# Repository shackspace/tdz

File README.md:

Teleduschzelle
==============

Teleduschzelle (phone shower cabin) is a project exco made happen @shackspace Stuttgart
 
http://shackspace.de/wiki/doku.php?id=project:teleduschzelle

Code will eventually appear here as well.

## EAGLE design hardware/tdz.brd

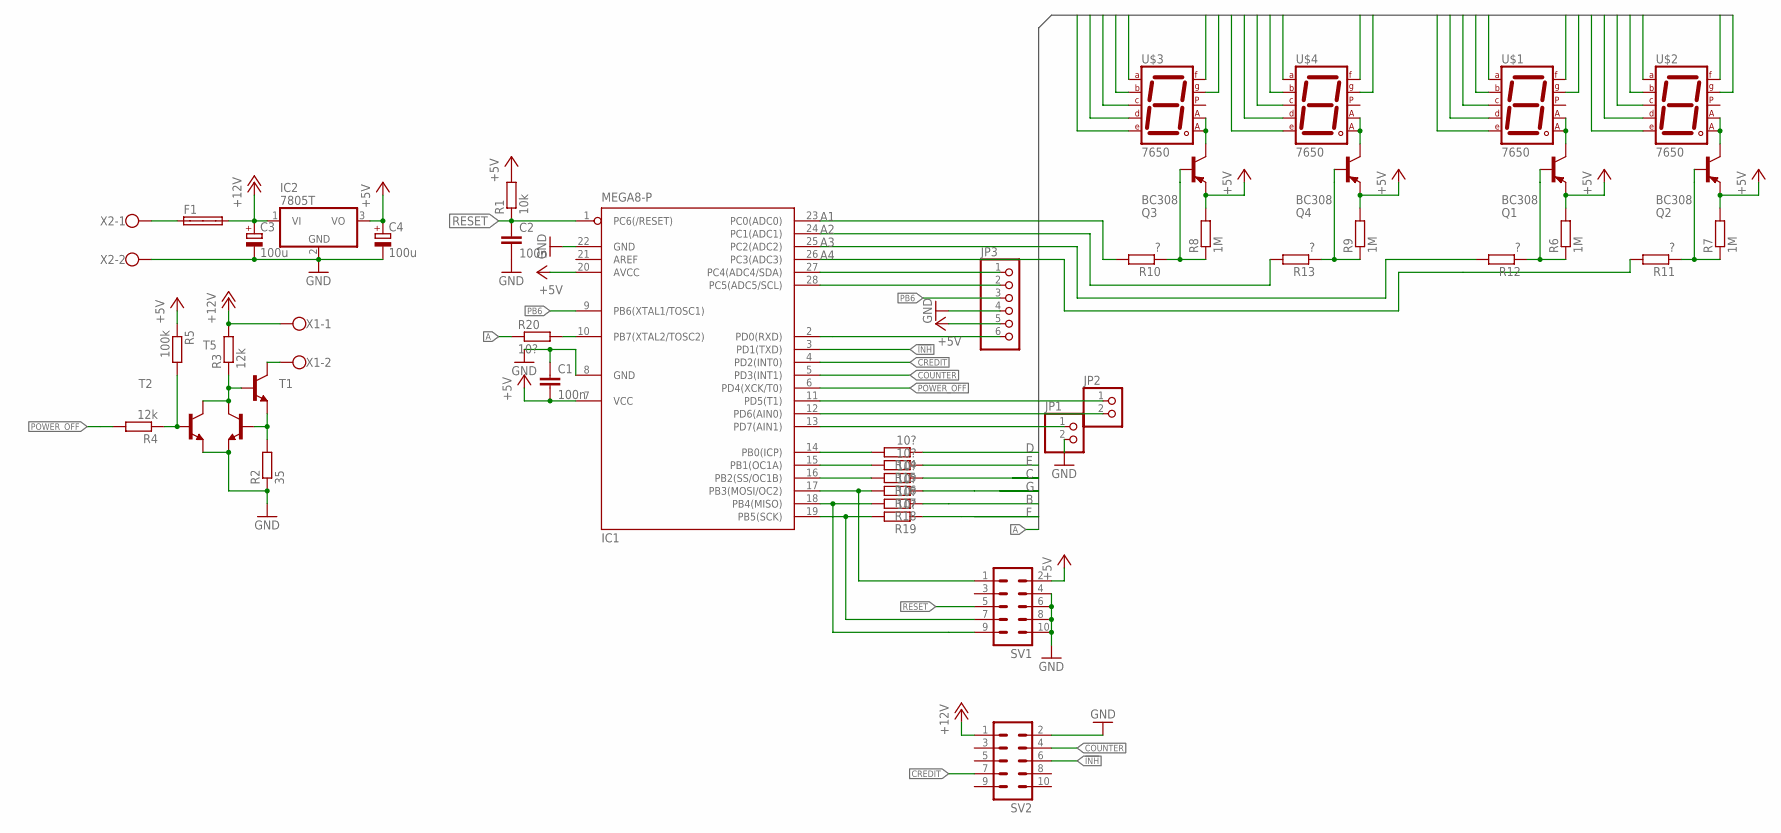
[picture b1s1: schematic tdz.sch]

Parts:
C1, C2: 100n; C0603
C3, C4: 100u; E22-9
F1: SHK20Q
IC1: MEGA8-P; DIL28-3
IC2: 7805T; TO220H
JP1, JP2: PINHD-1X02_2.54-S; 1X02-S
JP3: PINHD-1X6; 1X06
Q1, Q2, Q3, Q4: BC308; TO92-EBC
R1: 10k; R0603
R2: 35; R0603
R3, R4: 12k; R0603
R5: 100k; R0603
R6, R7, R8, R9: 1M; R0603
R10, R11, R12, R13: ?; 0207/7
R14, R15, R16, R17, R18, R19, R20: 10?; R0603
SV1, SV2: ML10L
T1, T2, T5: BC548-NPN-TO92-CBE; TO92-CBE
U$1, U$2, U$3, U$4: 7650
X1, X2: W237-102

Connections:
!INH!: IC1.3 (PD1(TXD)), SV2.6
+5V: C1.2, C4.+, IC1.7 (VCC), IC1.20 (AVCC), IC2.3 (VO), JP3.5, Q1.E, Q2.E, Q3.E, Q4.E, R1.2, R5.1, R6.2, R7.2, R8.2, R9.2, SV1.2
+12V: C3.+, F1.2A, IC2.1 (VI), R3.2, SV2.1, X1.1
A: R20.1, U$1.P$1 (A), U$2.P$1 (A), U$3.P$1 (A), U$4.P$1 (A)
A1: IC1.23 (PC0(ADC0)), R10.2
A2: IC1.24 (PC1(ADC1)), R13.2
A3: IC1.25 (PC2(ADC2)), R12.2
A4: IC1.26 (PC3(ADC3)), R11.2
B: R18.1, U$1.P$13 (B), U$2.P$13 (B), U$3.P$13 (B), U$4.P$13 (B)
C: R16.1, U$1.P$10 (C), U$2.P$10 (C), U$3.P$10 (C), U$4.P$10 (C)
COUNTER: IC1.5 (PD3(INT1)), SV2.4
CREDIT: IC1.4 (PD2(INT0)), SV2.7
D: R14.1, U$1.P$8 (D), U$2.P$8 (D), U$3.P$8 (D), U$4.P$8 (D)
E: R15.1, U$1.P$7 (E), U$2.P$7 (E), U$3.P$7 (E), U$4.P$7 (E)
F: R19.1, U$1.P$2 (F), U$2.P$2 (F), U$3.P$2 (F), U$4.P$2 (F)
G: R17.1, U$1.P$11 (G), U$2.P$11 (G), U$3.P$11 (G), U$4.P$11 (G)
GND: C1.1, C2.2, C3.-, C4.-, IC1.8 (GND), IC1.22 (GND), IC2.2 (GND), JP1.2, JP3.4, R2.1, SV1.4, SV1.6, SV1.8, SV1.10, SV2.2, T1.E, T2.E, X2.2
unnamed: Q1.C, U$1.P$3 (CA1), U$1.P$14 (CA2)
unnamed: Q2.C, U$2.P$3 (CA1), U$2.P$14 (CA2)
unnamed: Q3.C, U$3.P$3 (CA1), U$3.P$14 (CA2)
unnamed: Q4.C, U$4.P$3 (CA1), U$4.P$14 (CA2)
unnamed: Q4.B, R9.1, R13.1
unnamed: Q3.B, R8.1, R10.1
unnamed: Q2.B, R7.1, R11.1
unnamed: Q1.B, R6.1, R12.1
unnamed: T5.C, X1.2
unnamed: IC1.13 (PD7(AIN1)), JP1.1
unnamed: IC1.12 (PD6(AIN0)), JP2.2
unnamed: R2.2, T1.B, T5.E
unnamed: IC1.11 (PD5(T1)), JP2.1
unnamed: R3.1, T1.C, T2.C, T5.B
unnamed: R4.1, R5.2, T2.B
unnamed: IC1.10 (PB7(XTAL2/TOSC2)), R20.2
unnamed: IC1.14 (PB0(ICP)), R14.2
unnamed: IC1.15 (PB1(OC1A)), R15.2
unnamed: IC1.16 (PB2(SS/OC1B)), R16.2
unnamed: IC1.18 (PB4(MISO)), R18.2, SV1.9
unnamed: IC1.19 (PB5(SCK)), R19.2, SV1.7
unnamed: IC1.17 (PB3(MOSI/OC2)), R17.2, SV1.1
unnamed: IC1.27 (PC4(ADC4/SDA)), JP3.1
unnamed: IC1.28 (PC5(ADC5/SCL)), JP3.2
unnamed: IC1.2 (PD0(RXD)), JP3.6
unnamed: F1.1A, X2.1
PB6: IC1.9 (PB6(XTAL1/TOSC1)), JP3.3
POWER_OFF: IC1.6 (PD4(XCK/T0)), R4.2
RESET: C2.1, IC1.1 (PC6(/RESET)), R1.1, SV1.5

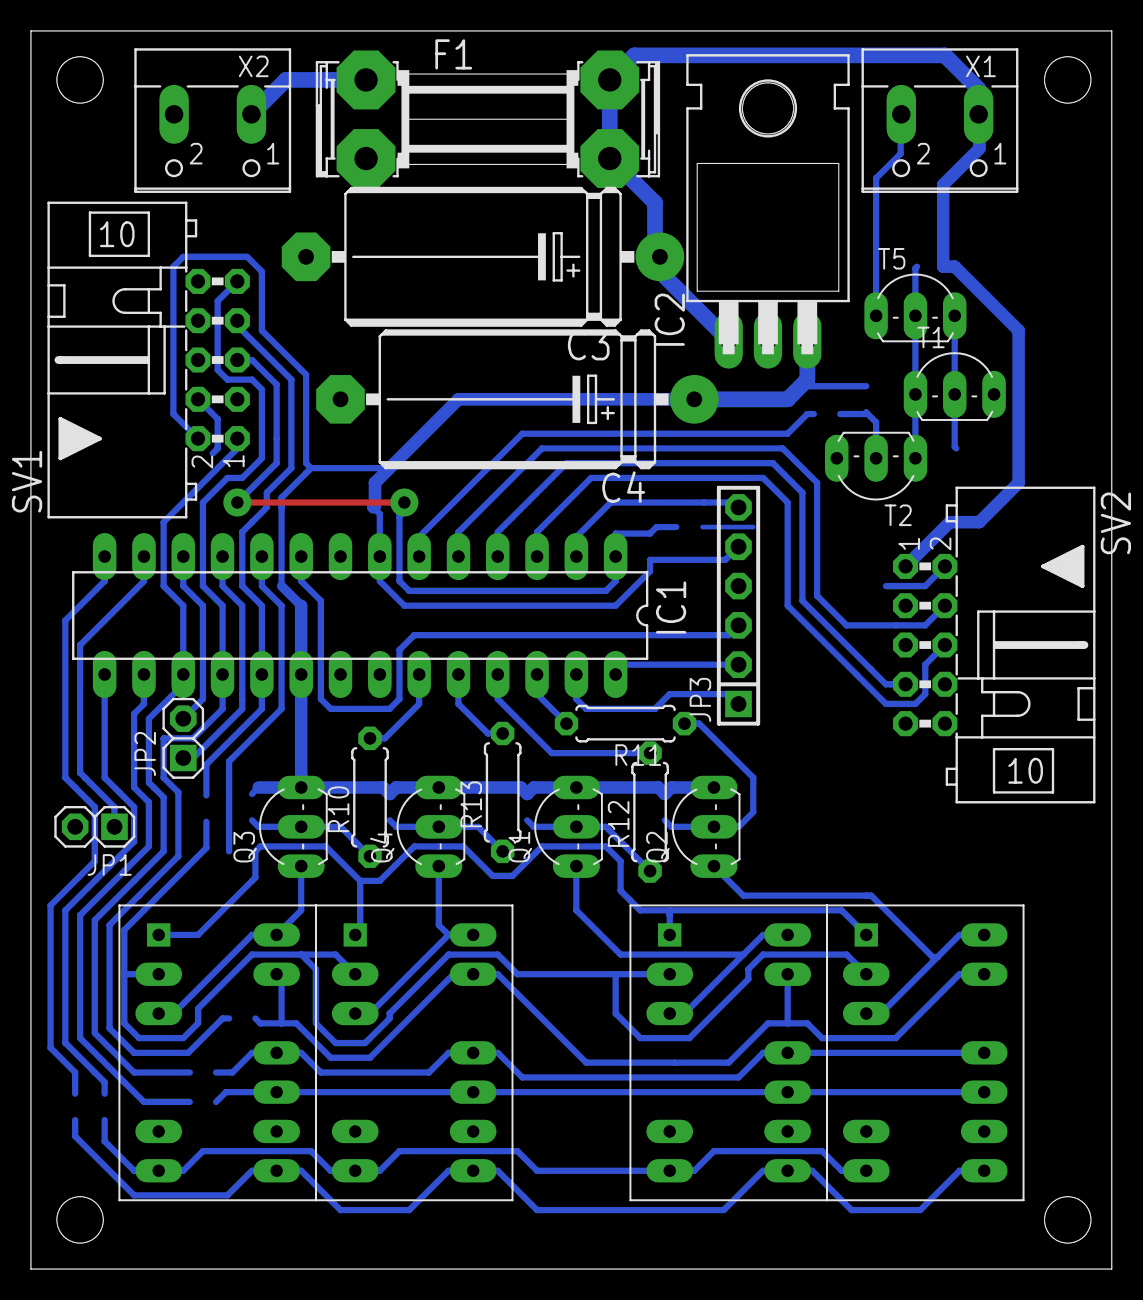
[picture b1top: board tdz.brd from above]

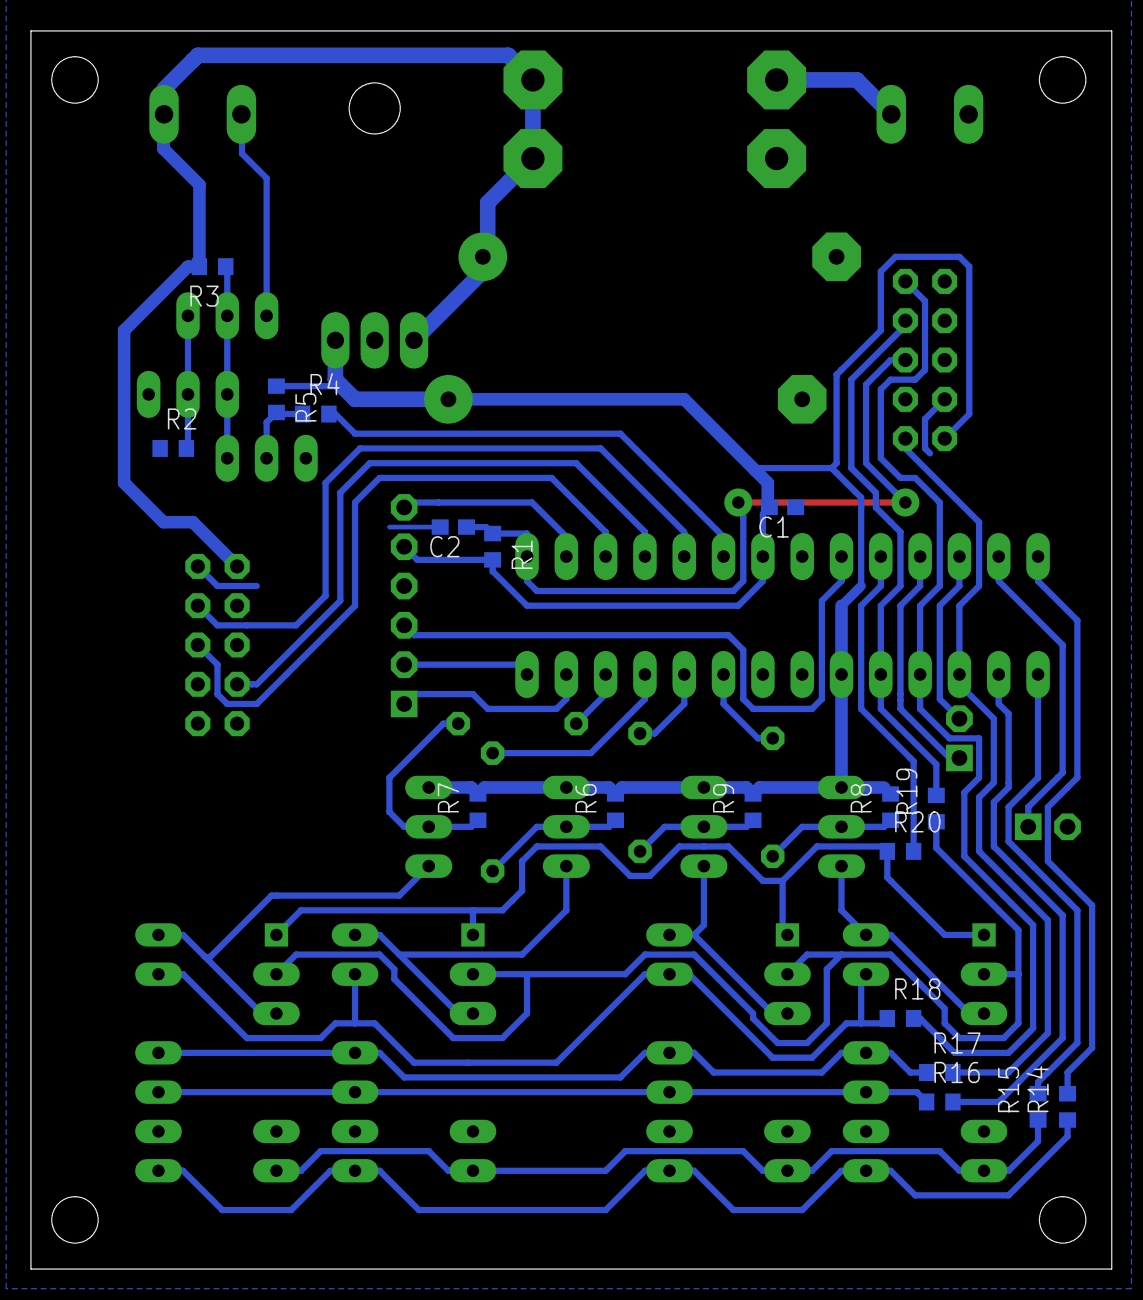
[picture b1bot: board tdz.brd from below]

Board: 2 copper layers, 69.8 x 80.0 mm, 45 parts (18 on the bottom side), 46 nets.

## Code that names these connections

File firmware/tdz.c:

/*
 * tdz.c
 *
 * Created: 14.06.2013 00:23:12
 *  Author: alex
 */


#include <avr/io.h>
#include <avr/interrupt.h>
#include <avr/pgmspace.h>
#include <avr/cpufunc.h>
#include <util/delay.h>
#include <string.h>

#define D	1<<PB0
#define E	1<<PB1
#define C	1<<PB2
#define G	1<<PB3
#define B	1<<PB4
#define F	1<<PB5
#define A	1<<PB7

#define S_0	(A|B|C|D|E|F)
#define S_1	(B|C)
#define S_2	(A|B|D|E|G)
#define S_3	(A|B|C|D|G)
#define S_4	(B|C|F|G)
#define S_5	(A|C|D|F|G)
#define S_6	(A|C|D|E|F|G)
#define S_7	(A|B|C)
#define S_8	(A|B|C|D|E|F|G)
#define S_9	(A|B|C|D|F|G)
#define S_E	(A|D|E|F|G)

const uint8_t symbols[] PROGMEM = {S_0,S_1,S_2,S_3,S_4,S_5,S_6,S_7,S_8,S_9};

#define T1_PRESCALER		1024
#define SECONDS_PER_50_C	300
#define BUZZER_THRESHOLD	60
#define DISPLAY_COUNT		4

volatile struct {
	uint16_t countdown;
	uint8_t display_digits[DISPLAY_COUNT];
}globals;


/*
 * Scans all 4 7-segment displays once
 * Run as often as possible
 */
void update7Seg(void){
	cli();																//We can't have this function interrupted or we risk destroying the displays
	for (uint8_t i=0;i<DISPLAY_COUNT;i++){
		if (globals.display_digits[i]>=sizeof(symbols)){
			//TODO: Possible error handling for invalid symbols
		}
		PORTB = (PORTB | 0b10111111) ^ (pgm_read_byte(symbols + globals.display_digits[i]));
		PORTC = (PORTC | 0b00001111) ^ (1<<i);
		_delay_us(10);
		PORTC |= 0b00001111;
		PORTB = 0b10111111;
	}
	PORTC |= 0b00001111;
	sei();
}


void start_timer1(void){
	TCNT1=0;
	TIMSK=1<<OCIE1A;
	OCR1A=F_CPU/T1_PRESCALER;
	TCCR1B=1<<CS12|1<<CS10|1<<WGM12;
}

/*
 * GPIO Assignments:
 * 	PORTB0-5,7	Output	Display Cathodes(active low)
 * 	PORTB6		Input	Unused	(Pullups on)
 *
 * 	PORTC0-3	Output	Display Anodes(active low)
 * 	PORTC4-5	Input	Unused	(Pullups on)
 *
 * 	PORTD0		Input	Unused	(Pullups on)
 * 	PORTD1		Output	INHIBIT	(active high)
 * 	PORTD2		Input	Credit	(Pullups on)
 * 	PORTD3		Input	Counter	(Pullups on)
 * 	PORTD4		Output	Power Off(active high)
 * 	PORTD5-7	Input	Unused	(Pullups on)
 */
inline void init_gpio(void){
	PORTB=0xFF;
	PORTC=0xFF;
	PORTD=0b11111101;
	DDRB=0b10111111;
	DDRC=0b00001111;
	DDRD=0b00010010;
}

inline void init_ext_interrupt(void){
	MCUCR=1<<ISC11;
	GICR=1<<INT1;
}

int main(void)
{
	init_gpio();
	init_ext_interrupt();
	memset(&globals,0,sizeof(globals));
	sei();
	while(1)
	{
		update7Seg();
	}
}

// Runs on the falling edge of the Counter signal
ISR(INT1_vect){
	// Check the interrupt pin multiple times to make sure it isn't just a glitch
	for(uint8_t i=20;i>0;i--){
		if (PIND & 1<<PD3){
			return;
		}
	}
	globals.countdown+=SECONDS_PER_50_C;
	PORTD&=~(1<<PD4);	//Enable the heater
	start_timer1();
}


// Runs every 1 second. Used to update the countdown timer and its BCD representation.
ISR(TIMER1_COMPA_vect){
	uint16_t minutes,seconds,countdown_temp;

	globals.countdown--;
	countdown_temp=globals.countdown;
	if (countdown_temp == 0){
		PORTD|=1<<PD4;	//Disable the heater
		TCCR1B=0;		//Deinit the timer
		TIMSK&=~(OCIE1A);
	}
//	else if (countdown_temp < BUZZER_THRESHOLD){
//		//TODO: Buzzer code here
//	}

	//Convert the numbers to full BCD
	minutes = countdown_temp/60;
	seconds = countdown_temp%60;
	if (minutes > 99){
		minutes = 99;
	}

	globals.display_digits[3]=seconds%10;
	globals.display_digits[2]=seconds/10;
	globals.display_digits[1]=minutes%10;
	globals.display_digits[0]=minutes/10;
}

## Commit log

2013-08-09 Readme stub.
2013-08-09 ignore file added
2013-08-13 updated to the used version for the door-twist-cover
    added the ad covers
2013-08-13 coinbox added file renamed
2013-09-08 Added firmware
2013-09-08 Added Eagle CAD files
